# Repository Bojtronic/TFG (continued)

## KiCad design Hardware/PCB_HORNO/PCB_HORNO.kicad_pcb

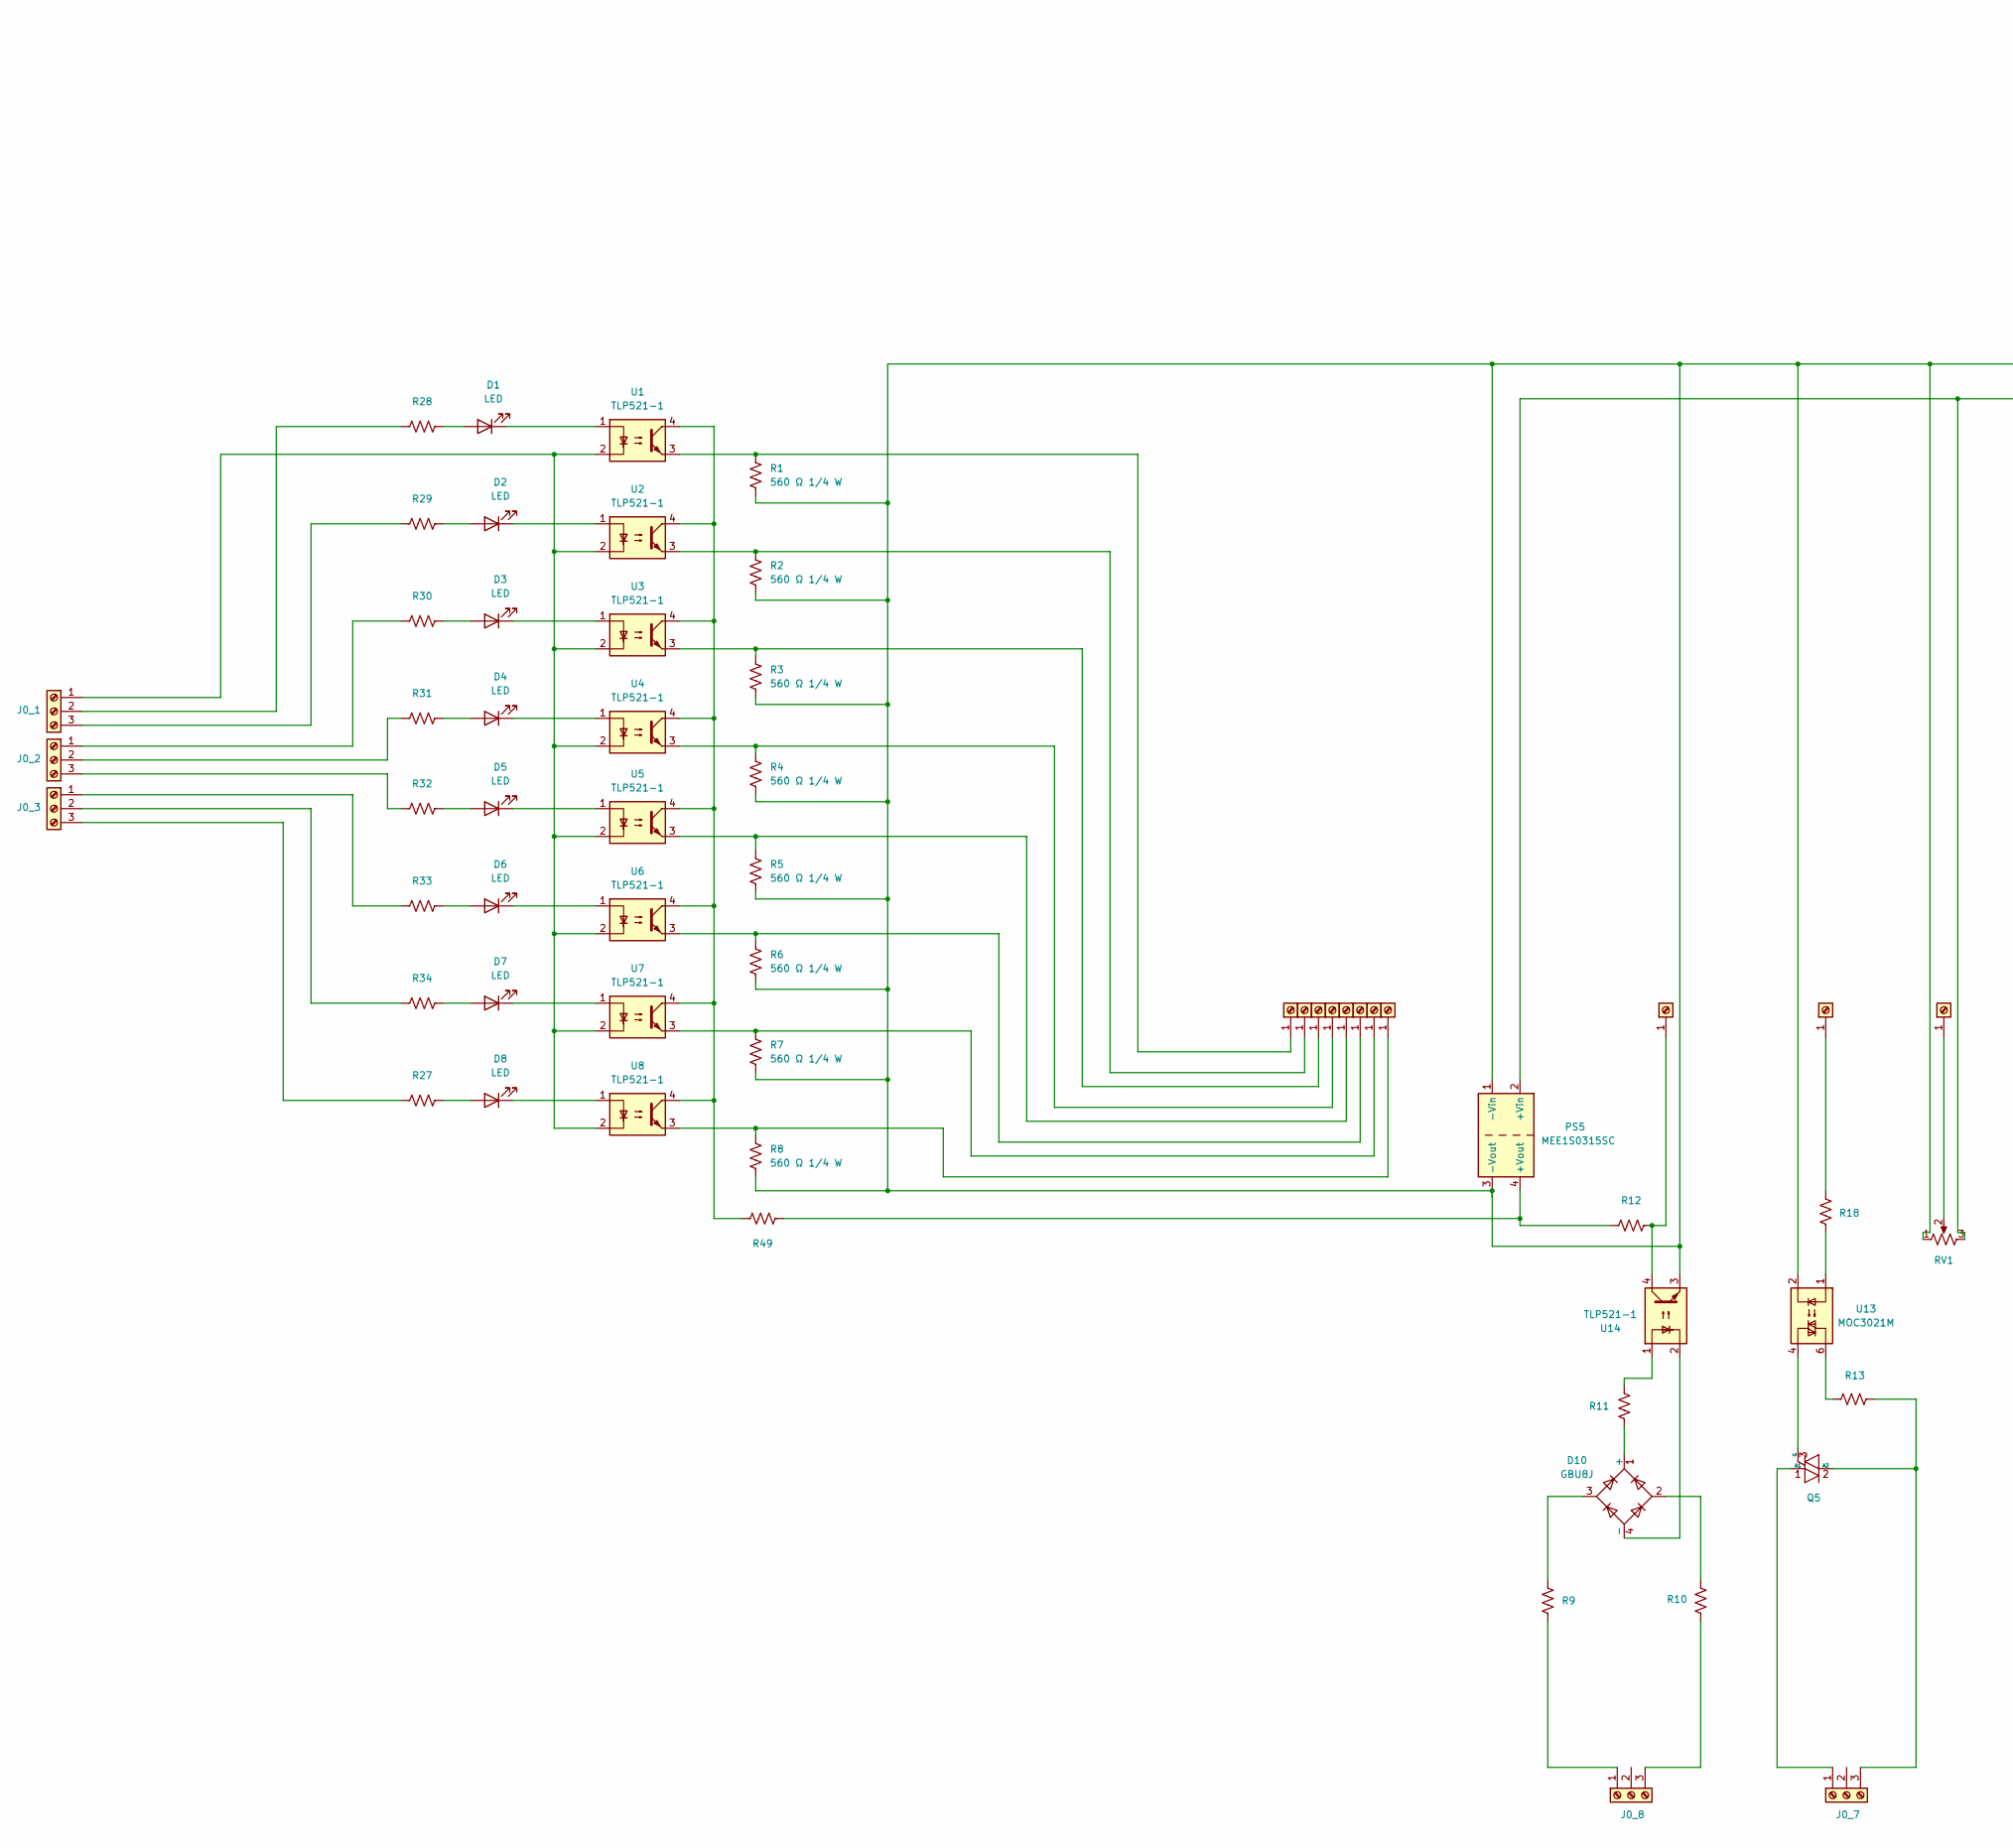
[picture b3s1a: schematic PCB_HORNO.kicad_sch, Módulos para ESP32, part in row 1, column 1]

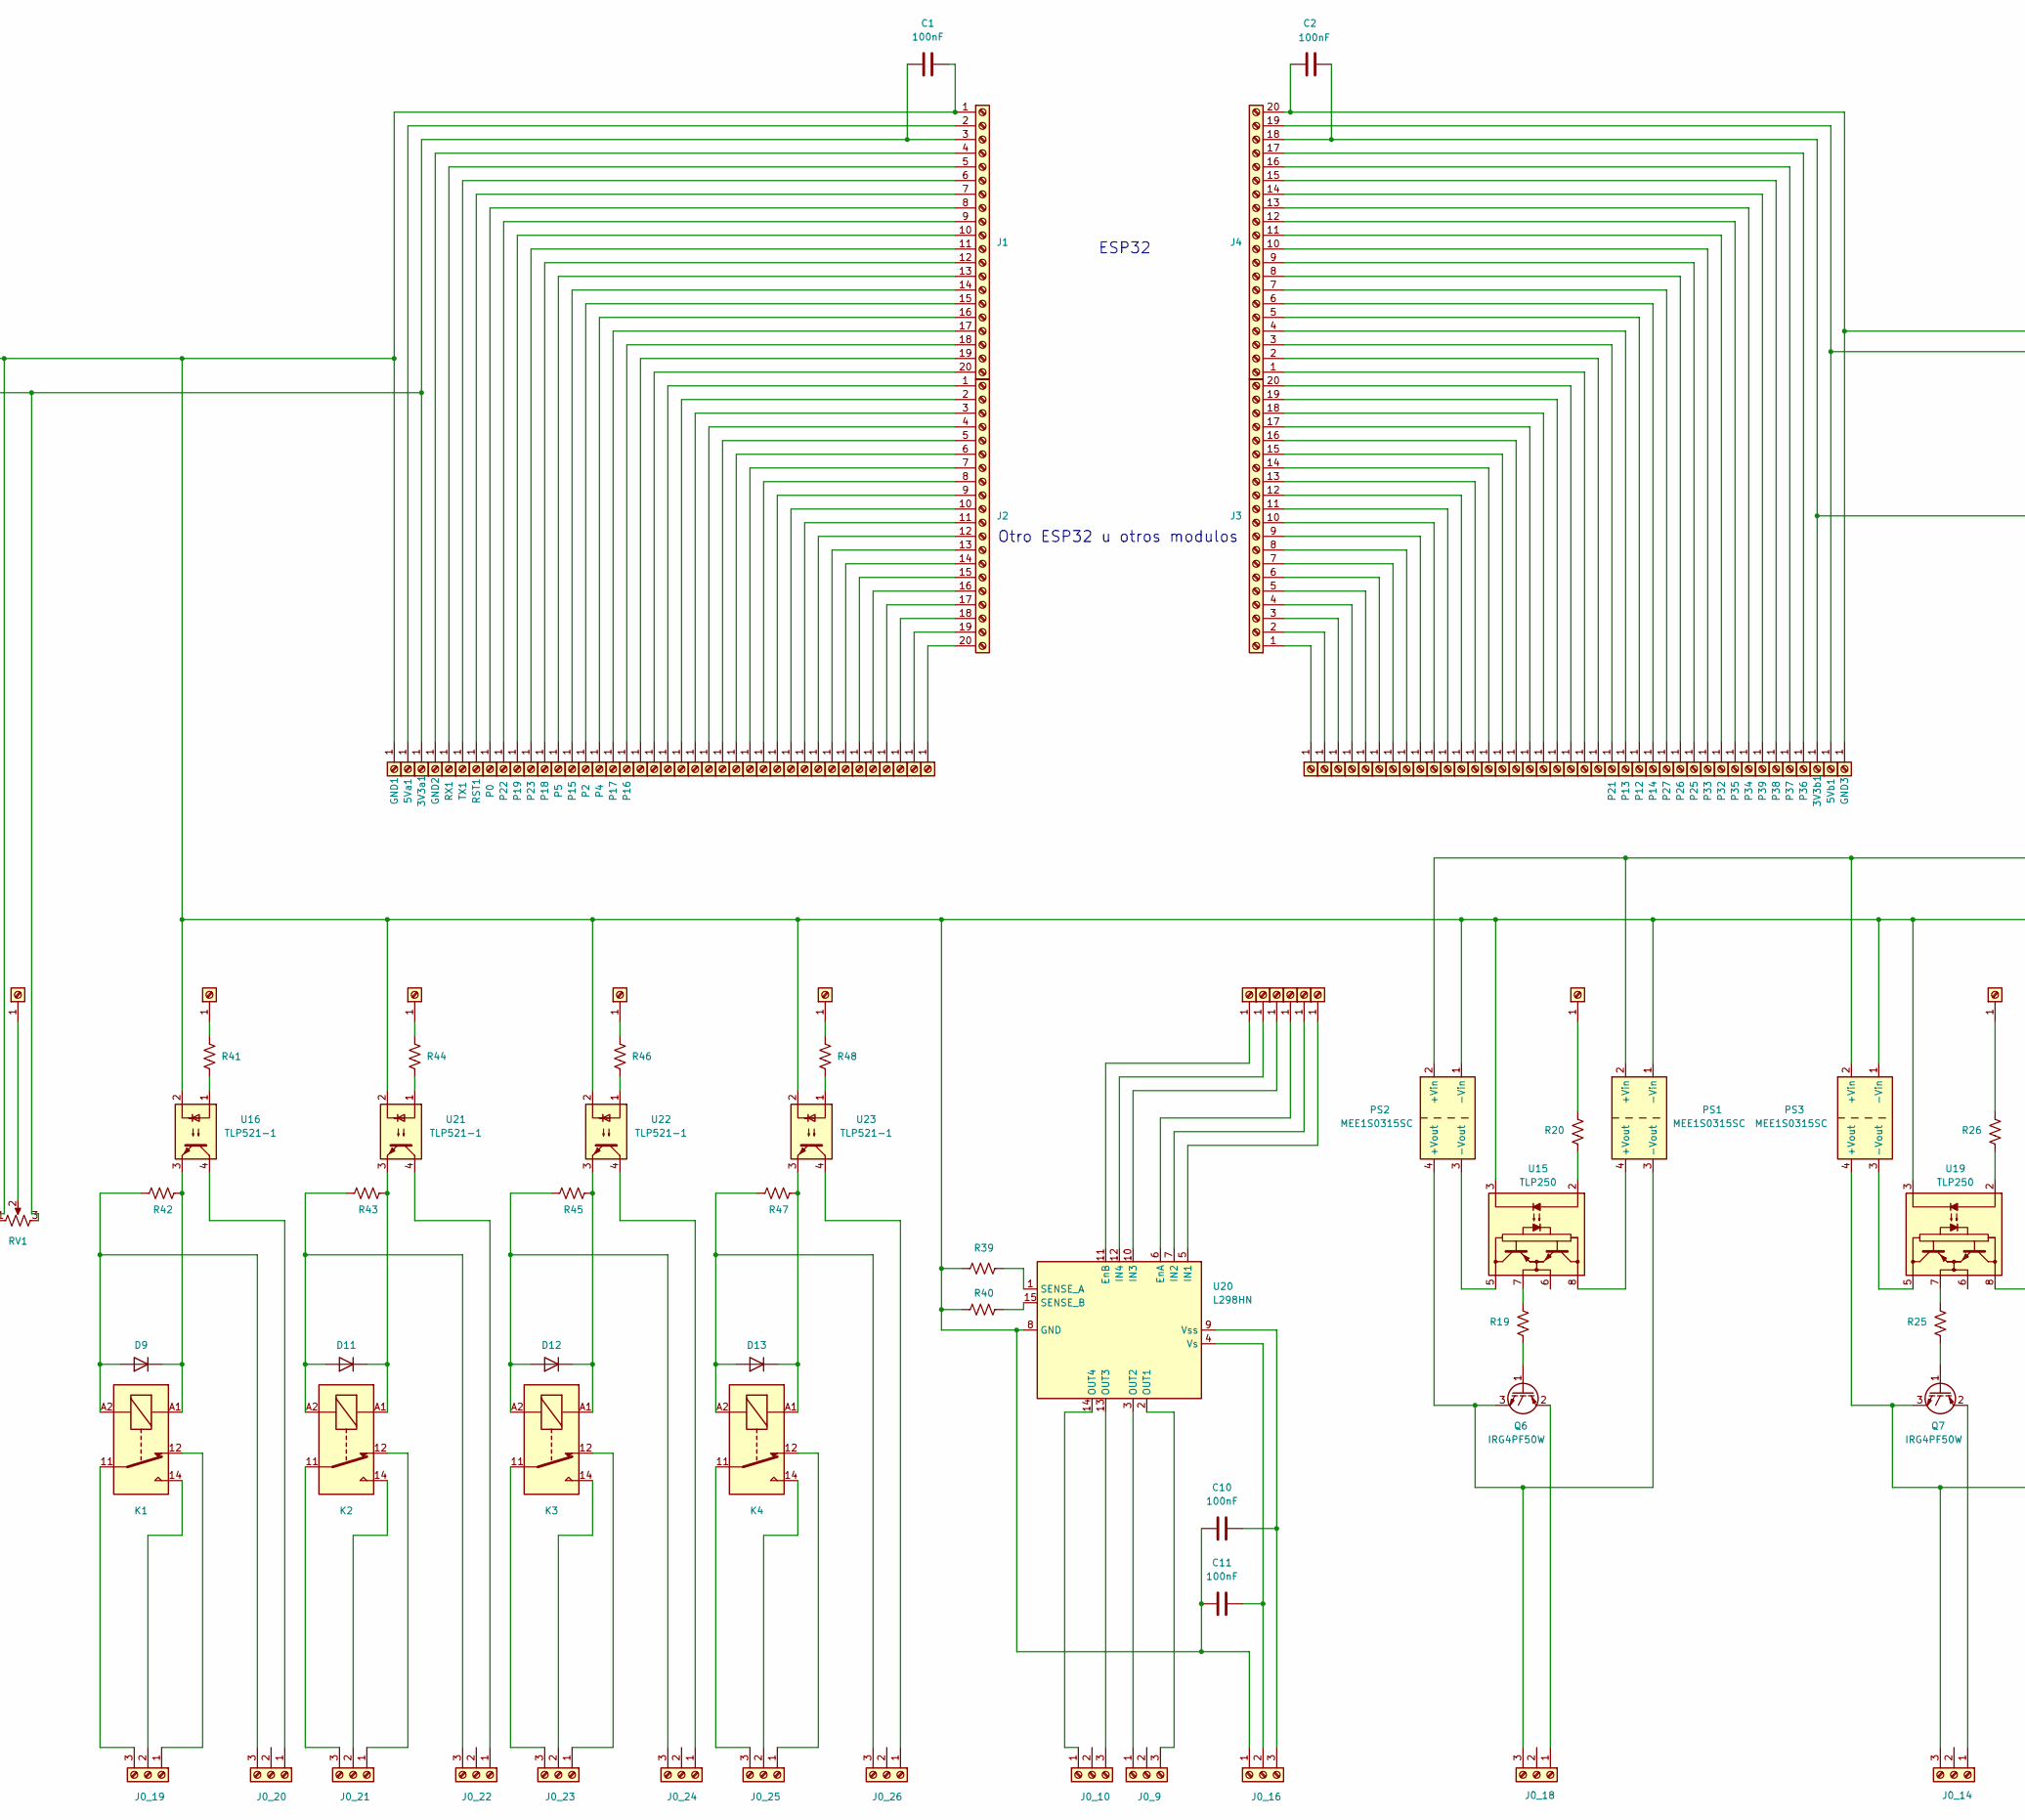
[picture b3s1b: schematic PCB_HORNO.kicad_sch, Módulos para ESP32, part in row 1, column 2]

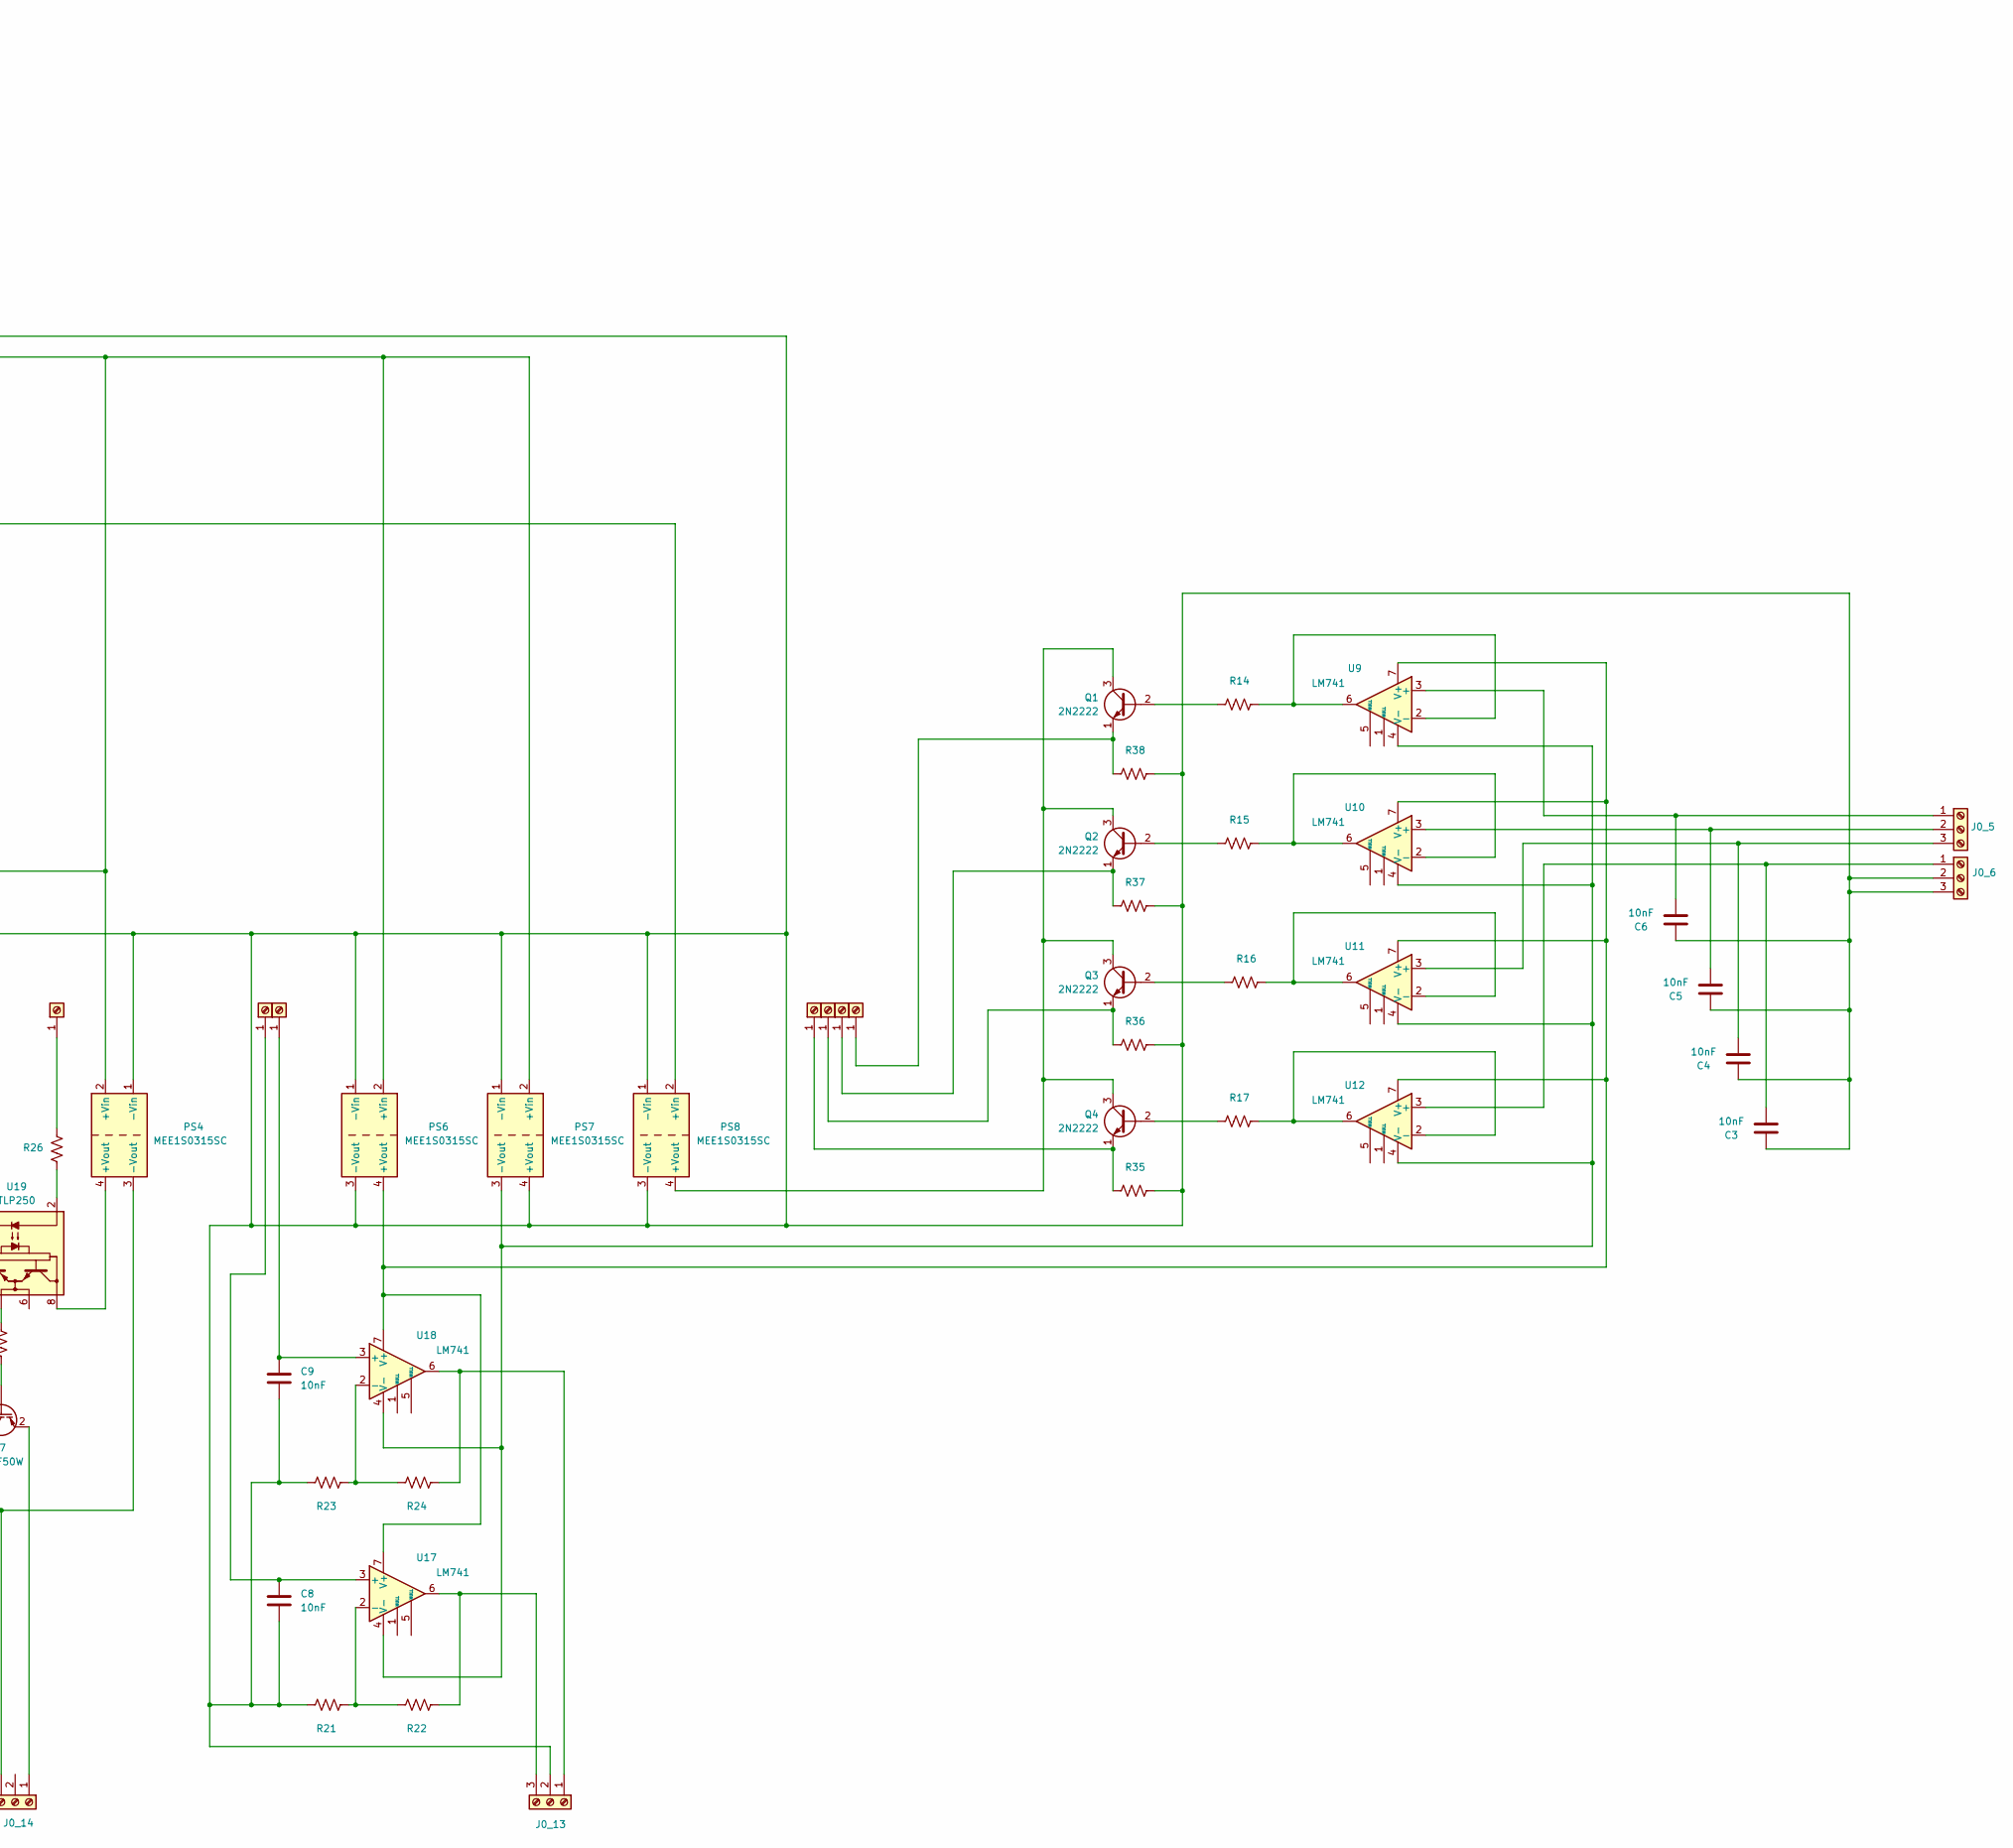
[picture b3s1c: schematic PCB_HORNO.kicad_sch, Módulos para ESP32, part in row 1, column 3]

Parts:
3V3a1, 3V3b1, 5Va1, 5Vb1: SolderWire-0.75sqmm_1x01_D1.25mm_OD2.3mm
C1, C2, C10, C11: 100nF; C_Disc_D5.1mm_W3.2mm_P5.00mm
C3, C4, C5, C6, C8, C9: 10nF; C_Disc_D5.1mm_W3.2mm_P5.00mm
D1, D2, D3, D4, D5, D6, D7, D8: LED; LED_D4.0mm
D9, D11, D12, D13: 1N4007; D_DO-41_SOD81_P10.16mm_Horizontal
D10: GBU8J; Diode_Bridge_Vishay_GBU
GND1, GND2, GND3: SolderWire-0.75sqmm_1x01_D1.25mm_OD2.3mm
J0_1, J0_2, J0_3, J0_5, J0_6, J0_7, J0_8, J0_9, J0_10, J0_13, J0_14, J0_16, J0_18, J0_19, J0_20, J0_21, J0_22, J0_23, J0_24, J0_25, J0_26: Screw_Terminal_01x03; TerminalBlock_Phoenix_PT-1,5-3-3.5-H_1x03_P3.50mm_Horizontal
J1, J2, J3, J4: Screw_Terminal_01x20; PinHeader_1x20_P2.54mm_Vertical
K1, K2, K3, K4: Fujitsu_FTR-LYCA005x; Relay_SPDT_Fujitsu_FTR-LYCA005x_FormC_Vertical
P0, P2, P4, P5, P12, P13, P14, P15, P16, P17, P18, P19, P21, P22, P23, P25, P26, P27, P32, P33, P34, P35, P36, P37, P38, P39: SolderWire-0.75sqmm_1x01_D1.25mm_OD2.3mm
PS1, PS2, PS3, PS4, PS5, PS6, PS7, PS8: MEE1S0315SC; Converter_DCDC_Murata_MEE1SxxxxSC_THT
PX1, PX2, PX3, PX4, PX5, PX6, PX7, PX8, PX9, PX10, PX11, PX12, PX13, PX14, PX15, PX16, PX17, PX18, PX19, PX20, PX21, PX22, PX23, PX24, PX25, PX26, PX27, PX28, PX29, PX30, PX31, PX32, PX33, PX34, PX35, PX36, PX37, PX38, PX39, PX40, PX41, PX42, PX43, PX44, PX45, PX46, PX47, PX48, PX49, PX50, PX51, PX52, PX53, PX54, PX55, PX57, PX59, PX62, PX63, PX66, PX67, PX69, PX72, PX80, PX111, PX112, PX113, PX118, PX119, PX121, PX122, PX123, PX124: SolderWire-0.75sqmm_1x01_D1.25mm_OD2.3mm
Q1, Q2, Q3, Q4: 2N2222; TO-92
Q5: BTA16-800B; TO-220-3_Vertical
Q6, Q7: IRG4PF50W; TO-264-3_Vertical
R1, R2, R3, R4, R5, R6, R7, R8: 560 Ω 1/4 W; R_Axial_DIN0207_L6.3mm_D2.5mm_P10.16mm_Horizontal
R9, R10, R11: R_US; R_Axial_DIN0411_L9.9mm_D3.6mm_P25.40mm_Horizontal
R12, R14, R15, R16, R17, R18, R19, R20, R21, R22, R23, R24, R25, R26, R35, R36, R37, R38, R41, R44, R46, R48, R49: R_US; R_Axial_DIN0207_L6.3mm_D2.5mm_P10.16mm_Horizontal
R13, R27, R28, R29, R30, R31, R32, R33, R34, R39, R40, R42, R43, R45, R47: R_US; R_Axial_DIN0309_L9.0mm_D3.2mm_P15.24mm_Horizontal
RST1: SolderWire-0.75sqmm_1x01_D1.25mm_OD2.3mm
RV1: R_Potentiometer_US; Potentiometer_Bourns_3266W_Vertical
RX1: SolderWire-0.75sqmm_1x01_D1.25mm_OD2.3mm
TX1: SolderWire-0.75sqmm_1x01_D1.25mm_OD2.3mm
U1, U2, U3, U4, U5, U6, U7, U8, U14, U16, U21, U22, U23: TLP521-1; DIP-4_W7.62mm
U9, U10, U11, U12, U17, U18: LM741; LM741_TH
U13: MOC3021M; DIP-6_W7.62mm
U15, U19: TLP250; DIP-8_W7.62mm
U20: L298HN; TO-220-15_P2.54x2.54mm_StaggerOdd_Lead5.84mm_TabDown

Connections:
unnamed: 3V3a1.1, C1.1, J1.3, PS5.2 (+Vin), RV1.3
unnamed: 3V3b1.1, C2.1, J4.18, PS8.2 (+Vin)
unnamed: 5Va1.1, J1.2
unnamed: 5Vb1.1, J4.19, PS1.2 (+Vin), PS2.2 (+Vin), PS3.2 (+Vin), PS4.2 (+Vin), PS6.2 (+Vin), PS7.2 (+Vin)
unnamed: D1.2 (A), R28.2
unnamed: D1.1 (K), U1.1
unnamed: D2.2 (A), R29.2
unnamed: D2.1 (K), U2.1
unnamed: D3.2 (A), R30.2
unnamed: D3.1 (K), U3.1
unnamed: D4.2 (A), R31.2
unnamed: D4.1 (K), U4.1
unnamed: D5.2 (A), R32.2
unnamed: D5.1 (K), U5.1
unnamed: D6.2 (A), R33.2
unnamed: D6.1 (K), U6.1
unnamed: D7.2 (A), R34.2
unnamed: D7.1 (K), U7.1
unnamed: D8.2 (A), R27.2
unnamed: D8.1 (K), U8.1
unnamed: D9.2 (A), J0_20.3, K1.A2, R42.1
unnamed: D9.1 (K), K1.A1, R42.2, U16.3
unnamed: D10.1 (+), R11.1
unnamed: D10.4 (-), U14.2
unnamed: D10.2, R10.2
unnamed: D10.3, R9.2
unnamed: D11.2 (A), J0_22.3, K2.A2, R43.1
unnamed: D11.1 (K), K2.A1, R43.2, U21.3
unnamed: D12.2 (A), J0_24.3, K3.A2, R45.1
unnamed: D12.1 (K), K3.A1, R45.2, U22.3
unnamed: D13.2 (A), J0_26.3, K4.A2, R47.1
unnamed: D13.1 (K), K4.A1, R47.2, U23.3
unnamed: C1.2, C2.2, C3.2, C4.2, C5.2, C6.2, C8.2, C9.2, C10.1, C11.1, GND1.1, GND3.1, J0_6.2, J0_6.3, J0_13.2, J0_16.1, J1.1, J4.20, PS1.1 (-Vin), PS2.1 (-Vin), PS3.1 (-Vin), PS4.1 (-Vin), PS5.1 (-Vin), PS5.3 (-Vout), PS6.1 (-Vin), PS6.3 (-Vout), PS7.1 (-Vin), PS7.4 (+Vout), PS8.1 (-Vin), PS8.3 (-Vout), R1.2, R2.2, R3.2, R4.2, R5.2, R6.2, R7.2, R8.2, R21.2, R23.2, R35.2, R36.2, R37.2, R38.2, R39.1, R40.1, RV1.1, U13.2, U14.3, U15.3 (C), U16.2, U19.3 (C), U20.8 (GND), U21.2, U22.2, U23.2
unnamed: GND2.1, J1.4
unnamed: J0_1.1, U1.2, U2.2, U3.2, U4.2, U5.2, U6.2, U7.2, U8.2
unnamed: J0_1.2, R28.1
unnamed: J0_1.3, R29.1
unnamed: J0_2.1, R30.1
unnamed: J0_2.2, R31.1
unnamed: J0_2.3, R32.1
unnamed: J0_3.1, R33.1
unnamed: J0_3.2, R34.1
unnamed: J0_3.3, R27.1
unnamed: C6.1, J0_5.1, U9.3 (+)
unnamed: C5.1, J0_5.2, U10.3 (+)
unnamed: C4.1, J0_5.3, U11.3 (+)
unnamed: C3.1, J0_6.1, U12.3 (+)
unnamed: J0_7.1, Q5.1 (A1)
unnamed: J0_7.3, Q5.2 (A2), R13.2
unnamed: J0_8.1, R9.1
unnamed: J0_8.3, R10.1
unnamed: J0_9.1, U20.3 (OUT2)
unnamed: J0_9.3, U20.2 (OUT1)
unnamed: J0_10.1, U20.14 (OUT4)
unnamed: J0_10.3, U20.13 (OUT3)
unnamed: J0_13.1, R24.1, U18.6
unnamed: J0_13.3, R22.1, U17.6
unnamed: J0_14.1, Q7.2 (C)
unnamed: J0_14.3, PS3.4 (+Vout), PS4.3 (-Vout), Q7.3 (E)
unnamed: C11.2, J0_16.2, U20.4 (Vs)
unnamed: C10.2, J0_16.3, U20.9 (Vss)
unnamed: J0_18.1, Q6.2 (C)
unnamed: J0_18.3, PS1.3 (-Vout), PS2.4 (+Vout), Q6.3 (E)
unnamed: J0_19.1, K1.12
unnamed: J0_19.2, K1.14
unnamed: J0_19.3, K1.11
unnamed: J0_20.1, U16.4
unnamed: J0_21.1, K2.12
unnamed: J0_21.2, K2.14
unnamed: J0_21.3, K2.11
unnamed: J0_22.1, U21.4
unnamed: J0_23.1, K3.12
unnamed: J0_23.2, K3.14
unnamed: J0_23.3, K3.11
unnamed: J0_24.1, U22.4
unnamed: J0_25.1, K4.12
unnamed: J0_25.2, K4.14
unnamed: J0_25.3, K4.11
unnamed: J0_26.1, U23.4
unnamed: J1.5, RX1.1
unnamed: J1.6, TX1.1
unnamed: J1.7, RST1.1
unnamed: J1.8, P0.1
unnamed: J1.9, P22.1
unnamed: J1.10, P19.1
unnamed: J1.11, P23.1
unnamed: J1.12, P18.1
unnamed: J1.13, P5.1
unnamed: J1.14, P15.1
unnamed: J1.15, P2.1
unnamed: J1.16, P4.1
unnamed: J1.17, P17.1
unnamed: J1.18, P16.1
unnamed: J1.19, PX1.1
unnamed: J1.20, PX2.1
unnamed: J2.1, PX3.1
unnamed: J2.2, PX4.1
unnamed: J2.3, PX5.1
unnamed: J2.4, PX6.1
unnamed: J2.5, PX7.1
unnamed: J2.6, PX8.1
unnamed: J2.7, PX9.1
unnamed: J2.8, PX10.1
unnamed: J2.9, PX11.1
unnamed: J2.10, PX12.1
unnamed: J2.11, PX13.1
unnamed: J2.12, PX14.1
unnamed: J2.13, PX15.1
unnamed: J2.14, PX16.1
unnamed: J2.15, PX17.1
unnamed: J2.16, PX18.1
unnamed: J2.17, PX19.1
unnamed: J2.18, PX20.1
unnamed: J2.19, PX21.1
unnamed: J2.20, PX22.1
unnamed: J3.1, PX23.1
unnamed: J3.2, PX24.1
unnamed: J3.3, PX25.1
unnamed: J3.4, PX26.1
unnamed: J3.5, PX27.1
unnamed: J3.6, PX28.1
unnamed: J3.7, PX29.1
unnamed: J3.8, PX30.1
unnamed: J3.9, PX31.1
unnamed: J3.10, PX32.1
unnamed: J3.11, PX33.1
unnamed: J3.12, PX34.1
unnamed: J3.13, PX35.1
unnamed: J3.14, PX36.1
unnamed: J3.15, PX37.1
unnamed: J3.16, PX38.1
unnamed: J3.17, PX39.1
unnamed: J3.18, PX40.1
unnamed: J3.19, PX41.1
unnamed: J3.20, PX42.1
unnamed: J4.1, PX43.1
unnamed: J4.2, PX44.1
unnamed: J4.3, P21.1
unnamed: J4.4, P13.1
unnamed: J4.5, P12.1
unnamed: J4.6, P14.1
unnamed: J4.7, P27.1
unnamed: J4.8, P26.1
unnamed: J4.9, P25.1
unnamed: J4.10, P33.1
unnamed: J4.11, P32.1
unnamed: J4.12, P35.1
unnamed: J4.13, P34.1
unnamed: J4.14, P39.1
unnamed: J4.15, P38.1
unnamed: J4.16, P37.1
unnamed: J4.17, P36.1
unnamed: PS1.4 (+Vout), U15.8 (VCC)
unnamed: PS2.3 (-Vout), U15.5 (VEE)
unnamed: PS3.3 (-Vout), U19.5 (VEE)
unnamed: PS4.4 (+Vout), U19.8 (VCC)
unnamed: PS5.4 (+Vout), R12.1, R49.1
unnamed: PS6.4 (+Vout), U9.7 (V+), U10.7 (V+), U11.7 (V+), U12.7 (V+), U17.7 (V+), U18.7 (V+)
unnamed: PS7.3 (-Vout), U9.4 (V-), U10.4 (V-), U11.4 (V-), U12.4 (V-), U17.4 (V-), U18.4 (V-)
unnamed: PS8.4 (+Vout), Q1.3 (C), Q2.3 (C), Q3.3 (C), Q4.3 (C)
unnamed: PX45.1, U20.11 (EnB)
unnamed: PX46.1, R1.1, U1.3
unnamed: PX47.1, R2.1, U2.3
unnamed: PX48.1, R3.1, U3.3
unnamed: PX49.1, R4.1, U4.3
unnamed: PX50.1, R5.1, U5.3
unnamed: PX51.1, R6.1, U6.3
unnamed: PX52.1, R7.1, U7.3
unnamed: PX53.1, R8.1, U8.3
unnamed: PX54.1, R12.2, U14.4
unnamed: PX55.1, U20.6 (EnA)
unnamed: PX57.1, R18.1
unnamed: PX59.1, RV1.2
unnamed: PX62.1, U20.12 (IN4)
unnamed: PX63.1, R44.2
unnamed: PX66.1, R20.2
unnamed: PX67.1, R46.2
unnamed: PX69.1, R41.2
unnamed: PX72.1, R48.2
unnamed: PX80.1, R26.2
unnamed: PX111.1, U20.10 (IN3)
unnamed: PX112.1, U20.7 (IN2)
unnamed: PX113.1, U20.5 (IN1)
unnamed: C8.1, PX118.1, U17.3 (+)
unnamed: C9.1, PX119.1, U18.3 (+)
unnamed: PX121.1, Q4.1 (E), R35.1
unnamed: PX122.1, Q3.1 (E), R36.1
unnamed: PX123.1, Q2.1 (E), R37.1
unnamed: PX124.1, Q1.1 (E), R38.1
unnamed: Q1.2 (B), R14.1
unnamed: Q2.2 (B), R15.1
unnamed: Q3.2 (B), R16.1
unnamed: Q4.2 (B), R17.1
unnamed: Q5.3 (G), U13.4
unnamed: Q6.1 (G), R19.1
unnamed: Q7.1 (G), R25.1
unnamed: R11.2, U14.1
unnamed: R13.1, U13.6
unnamed: R18.2, U13.1
unnamed: R19.2, U15.7 (VO)
unnamed: R25.2, U19.7 (VO)
unnamed: R41.1, U16.1
unnamed: R44.1, U21.1
unnamed: R46.1, U22.1
unnamed: R48.1, U23.1
unnamed: R49.2, U1.4, U2.4, U3.4, U4.4, U5.4, U6.4, U7.4, U8.4
unnamed: R14.2, U9.2 (-), U9.6
unnamed: R15.2, U10.2 (-), U10.6
unnamed: R16.2, U11.2 (-), U11.6
unnamed: R17.2, U12.2 (-), U12.6
unnamed: R20.1, U15.2 (A)
unnamed: R21.1, R22.2, U17.2 (-)
unnamed: R23.1, R24.2, U18.2 (-)
unnamed: R26.1, U19.2 (A)
unnamed: R39.2, U20.1 (SENSE_A)
unnamed: R40.2, U20.15 (SENSE_B)

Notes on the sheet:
Otro ESP32 u otros modulos
ESP32

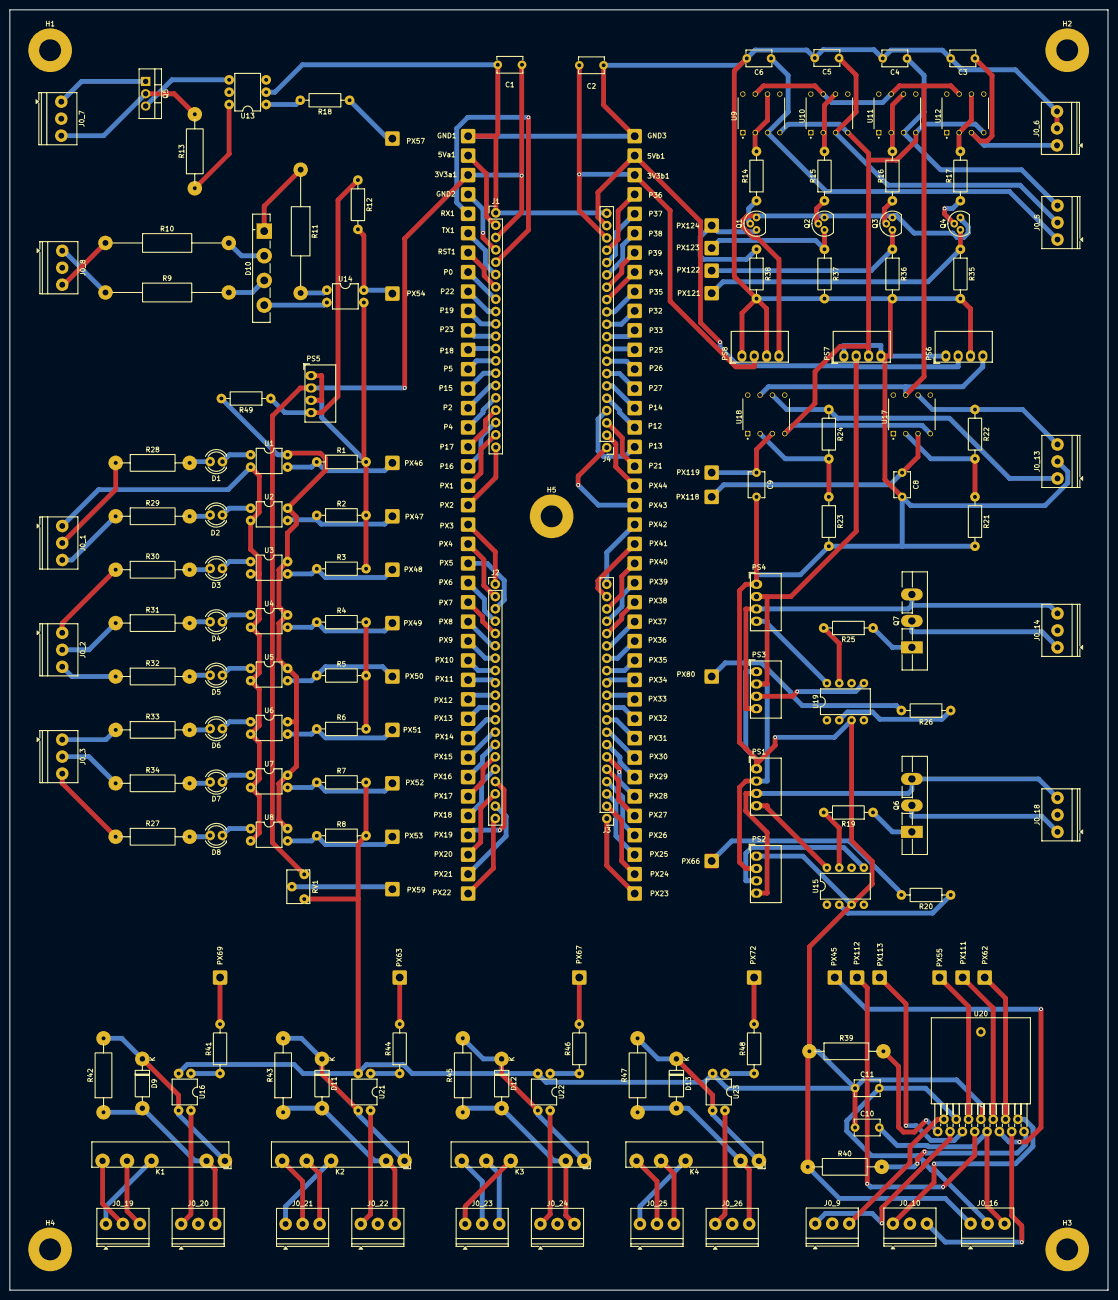
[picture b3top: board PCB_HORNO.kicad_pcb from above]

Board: 2 copper layers, 226.2 x 263.7 mm, 254 parts (0 on the bottom side), 216 nets.

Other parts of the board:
H1, H2, H3, H4, H5: MountingHole_4.5mm_Pad

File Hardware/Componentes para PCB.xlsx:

Nombre | Cantidad | Numero de parte - Valor | Referencia | Datasheet | Footprint
C1,C2,C10,C11 | 4.0 | 100nF | AD10187 https://www.microjpm.com/products/a100if-100v-capacitor-poli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 | ~ | Capacitor_THT:C_Disc_D5.1mm_W3.2mm_P5.00mm
C3,C4,C5,C6,C8,C9 | 6.0 | 10nF | AD11887 https://www.microjpm.com/products/a0-01uf-50v-capacitor-ceramico/ | ~ | Capacitor_THT:C_Disc_D5.1mm_W3.2mm_P5.00mm
D1,D2,D3,D4,D5,D6,D7,D8 | 8.0 | LED |  | ~ | LED_THT:LED_D4.0mm
D9,D11,D12,D13 | 4.0 | 1N4007 | AD12190 https://www.microjpm.com/products/a1n4007-diodo-rectificador/ | http://www.vishay.com/docs/88503/1n4001.pdf | Diode_THT:D_DO-41_SOD81_P10.16mm_Horizontal
D10 | 1.0 | GBU8J |  | https://www.alldatasheet.com/html-pdf/1923901/ONSEMI/GBU8J/2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 | Diode_THT:Diode_Bridge_Vishay_GBU
J0_1,J0_2,J0_3,J0_5,J0_6,J0_7,J0_8,J0_9,J0_10,J0_13,J0_14,J0_16,J0_18,J0_19,J0_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 | 21.0 | Terminales de tornillo espaciados en 3.5mm |  | ~ | TerminalBlock_Phoenix:TerminalBlock_Phoenix_PT-1,5-3-3.5-H_1x03_P3.50mm_Horizon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
J1,J2,J3,J4 | 4.0 | 20 Pin 2.54mm Header Male Breakable | AD112 https://www.microjpm.com/products/conectores-rompibles-de-ba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 | ~ | Connector_PinHeader_2.54mm:PinHeader_1x20_P2.54mm_Vertical
K1,K2,K3,K4 | 4.0 | Fujitsu FTR-LYCA005x |  | https://www.alldatasheet.com/html-pdf/194908/FUJITSU/FTR-LY/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 | Relay_THT:Relay_SPDT_Fujitsu_FTR-LYCA005x_FormC_Vertical
PS1,PS4,PS6,PS7 | 4.0 | MEE1S0515SC |  | https://www.alldatasheet.com/html-pdf/528940/MURATA-PS/MEE1S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 | Converter_DCDC:Converter_DCDC_Murata_MEE1SxxxxSC_THT
PS2,PS3 | 2.0 | MEE1S0505SC |  | https://www.alldatasheet.com/html-pdf/528940/MURATA-PS/MEE1S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 | Converter_DCDC:Converter_DCDC_Murata_MEE1SxxxxSC_THT
PS5 | 1.0 | MEE1S0305SC |  | https://www.alldatasheet.com/html-pdf/528940/MURATA-PS/MEE1S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 | Converter_DCDC:Converter_DCDC_Murata_MEE1SxxxxSC_THT
PS8 | 1.0 | MEE1S0303SC |  | https://www.alldatasheet.com/html-pdf/528940/MURATA-PS/MEE1S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 | Converter_DCDC:Converter_DCDC_Murata_MEE1SxxxxSC_THT
Q1,Q2,Q3,Q4 | 4.0 | 2N2222 | AD517 https://www.microjpm.com/products/a2n2222/ | https://c1555f5ec9.clvaw-cdnwnd.com/34662fcf1f1e607c56144243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 | Package_TO_SOT_THT:TO-92
Q5 | 1.0 | BTA16-800B |  | https://www.st.com/resource/en/datasheet/bta16.pdf | Package_TO_SOT_THT:TO-220-3_Vertical
Q6,Q7 | 2.0 | IRG4PF50W |  | https://www.alldatasheet.com/html-pdf/116087/IRF/IRG4PF50W/5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 | Package_TO_SOT_THT:TO-264-3_Vertical
R1,R2,R3,R4,R5,R6,R7,R8 | 8.0 | 560Ω - 1/4 W |  | ~ | Resistor_THT:R_Axial_DIN0207_L6.3mm_D2.5mm_P10.16mm_Horizontal
R9,R10,R11 | 3.0 | Depende de aplicación cruce por cero |  | ~ | Resistor_THT:R_Axial_DIN0411_L9.9mm_D3.6mm_P25.40mm_Horizontal
R12 | 1.0 | 330Ω - 1/4 W |  | ~ | Resistor_THT:R_Axial_DIN0207_L6.3mm_D2.5mm_P10.16mm_Horizontal
R13 | 1.0 | Depende de aplicación disparo con triac |  | ~ | Resistor_THT:R_Axial_DIN0309_L9.0mm_D3.2mm_P15.24mm_Horizontal
R14,R15,R16,R17 | 4.0 | 7.5KΩ - 1/4 W |  | ~ | Resistor_THT:R_Axial_DIN0207_L6.3mm_D2.5mm_P10.16mm_Horizontal
R19,R25 | 2.0 | 10Ω - 1/4 W |  | ~ | Resistor_THT:R_Axial_DIN0207_L6.3mm_D2.5mm_P10.16mm_Horizontal
R18,R20,R26,R41,R44,R46,R48 | 6.0 | 270Ω - 1/4 W |  | ~ | Resistor_THT:R_Axial_DIN0207_L6.3mm_D2.5mm_P10.16mm_Horizontal
R21,R22,R23,R24 | 4.0 | Depende de la aplicación salida analógica |  | ~ | Resistor_THT:R_Axial_DIN0207_L6.3mm_D2.5mm_P10.16mm_Horizontal
R27,R28,R29,R30,R31,R32,R33,R34,R49 | 8.0 | 100 Ω - 1/4 W |  | ~ | Resistor_THT:R_Axial_DIN0309_L9.0mm_D3.2mm_P15.24mm_Horizontal
R35,R36,R37,R38 | 4.0 | 39Ω - 1/4 W |  | ~ | Resistor_THT:R_Axial_DIN0207_L6.3mm_D2.5mm_P10.16mm_Horizontal
R39,R40 | 2.0 | Depende de la aplicación puente H |  | ~ | Resistor_THT:R_Axial_DIN0309_L9.0mm_D3.2mm_P15.24mm_Horizontal
R42,R43,R45,R47 | 4.0 | Depende de la tensión aplicada a la bobina del rele |  | ~ | Resistor_THT:R_Axial_DIN0309_L9.0mm_D3.2mm_P15.24mm_Horizontal
RV1 | 1.0 | 10KΩ Bourns 3266W |  | https://www.alldatasheet.es/html-pdf/221234/BOURNS/3266/213/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 | Potentiometer_THT:Potentiometer_Bourns_3266W_Vertical
U1,U2,U3,U4,U5,U6,U7,U8,U14,U16,U21,U22,U23 | 13.0 | TLP521-1 |  | https://docs.rs-online.com/d620/0900766b800287f7.pdf | Package_DIP:DIP-4_W7.62mm
U9,U10,U11,U12,U17,U18 | 6.0 | LM741 |  | http://www.ti.com/lit/ds/symlink/lm741.pdf | LM741_TH:LM741_TH
U13 | 1.0 | MOC3021M | AD25788 https://www.microjpm.com/products/moc3021-optoiso-400vdrm-tr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 | https://www.onsemi.com/pub/Collateral/MOC3023M-D.PDF | Package_DIP:DIP-6_W7.62mm
U15,U19 | 2.0 | TLP250 |  | http://toshiba.semicon-storage.com/info/docget.jsp?did=16821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 | Package_DIP:DIP-8_W7.62mm
U20 | 1.0 | L298HN Multiwatt15 H | AD1603 https://www.microjpm.com/products/l298n/ | http://www.st.com/st-web-ui/static/active/en/resource/techni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 | Package_TO_SOT_THT:TO-220-15_P2.54x2.54mm_StaggerOdd_Lead5.84mm_TabDown
